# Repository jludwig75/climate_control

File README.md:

# Climate Control #

## Schematic ##

## PCB Board ##

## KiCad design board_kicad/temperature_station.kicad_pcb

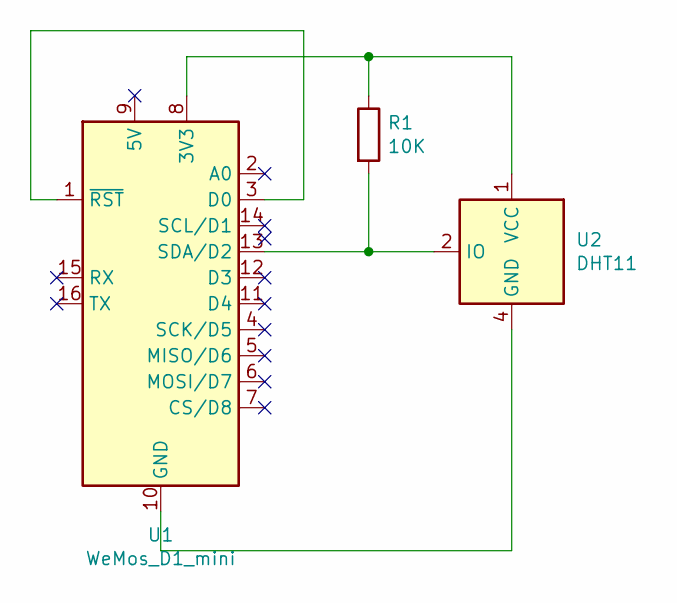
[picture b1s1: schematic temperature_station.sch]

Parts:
R1: 10K; R_Axial_DIN0207_L6.3mm_D2.5mm_P10.16mm_Horizontal
U1: WeMos_D1_mini; WEMOS_D1_mini_light
U2: DHT11; Aosong_DHT11_5.5x12.0_P2.54mm

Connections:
unnamed: R1.1, U1.8 (3V3), U2.1 (VCC)
unnamed: R1.2, U1.13 (SDA/D2), U2.2 (IO)
unnamed: U1.1 (~RST), U1.3 (D0)
unnamed: U1.10 (GND), U2.4 (GND)

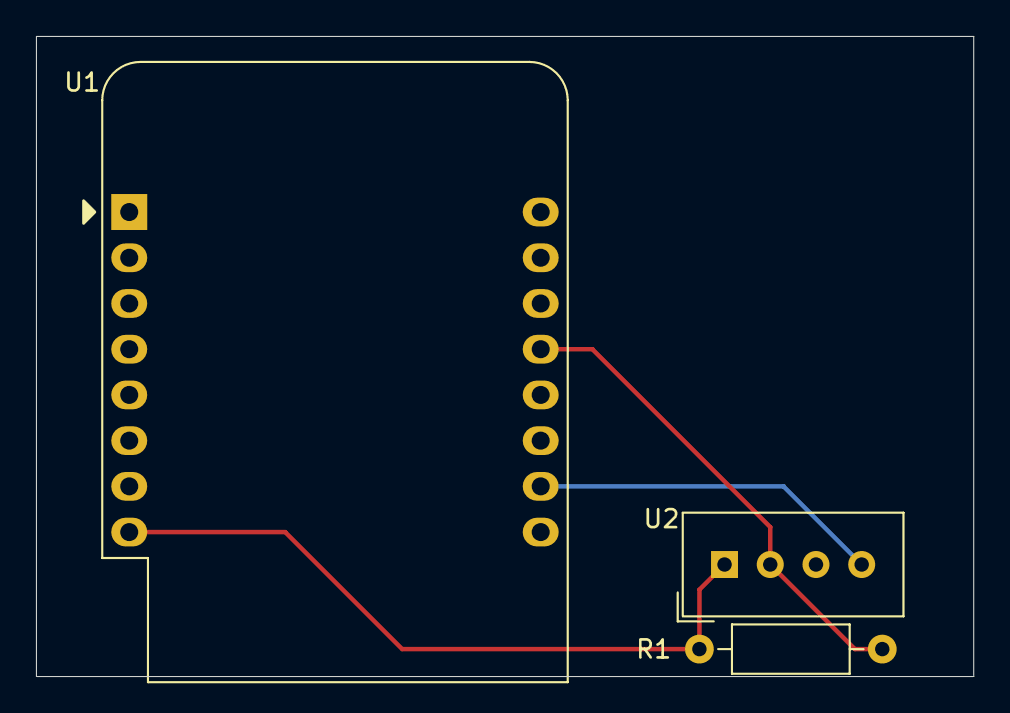
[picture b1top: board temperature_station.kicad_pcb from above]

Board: 2 copper layers, 52.1 x 35.6 mm, 3 parts (0 on the bottom side), 4 nets.

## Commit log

2020-12-19 Created repo
2020-12-19 Added control server
2020-12-19 Make control server script executable
2020-12-19 Start creating database
2020-12-19 Created database interface
2020-12-19 Added database interface test
2020-12-19 Fix ups to createDatabase and added method documentation
2020-12-19 Added 24-hour report display
2020-12-19 Report temperature as floating point
2020-12-19 Fix C++ compile errors
2020-12-20 Missed floating point conversion bug
2020-12-20 Store temperature in DB as float
2020-12-20 Set board to ESP-12E
2020-12-20 Fixed handle leak
2020-12-20 Cap vent sensor temperature to it can be viewed on the same graphs without messing up the range
2020-12-20 Bug fixes and enhancements
2020-12-20 Changed graph x axis to time uints
2020-12-20 Got refresh working
2020-12-21 Calculate and display thermostat state
2020-12-21 Impoved thermostat state calculation accuracy
2020-12-31 Added comment
2020-12-31 Added station VCC to report data
2020-12-31 Bug fixes
2020-12-31 Fix client bug
2020-12-31 Added OTA support
2020-12-31 Added webserver support for OTA initiation
2020-12-31 Split out seperate build envs in platformio.ini
2020-12-31 Moved station ID to platformio.ini
2020-12-31 Moved hostname to platformio.ini
2020-12-31 Put time limit on sensor data query
2020-12-31 Web page bug. Also only fetch as many data points as we plan to display
2020-12-31 Converted report webpage to vuej.js
2020-12-31 Fix ups
2021-01-01 Improved graph title
2021-01-01 Seprated control and report web servers. Made chart vue.js component.
2021-01-01 Added plots for all data points
2021-01-01 Fixed up variable names
2021-01-01 Removed static dir support from control server
2021-01-01 Add stations dynamically, supporting unlimited number of stations
2021-01-01 Cleanup plot code.
2021-01-01 Add plot legend
2021-01-01 Plural was wrong for plots
2021-01-01 Added ability to change end time for plot. Still needs cleanup
2021-01-02 Basic functionality to change days with forward and back buttons. Still a bug and enhancement.
2021-01-02 Changed date/time adjust interval to be display interval
2021-01-02 Display current station data on plot legend
2021-01-02 Add button to move historical data view to now.
2021-01-05 DB code fixes
2021-01-06 Start transition to MQTT
2021-01-07 Switch sensor data updates to mqtt
2021-01-07 Specify sensor data update message type
2021-01-07 Strat moving update control to MQTT
2021-01-07 Added missing files. Got MQTT update started
2021-01-07 More work on update control script
2021-01-07 Fixups to update control script
2021-01-08 Added new update script with mock station for test
2021-01-08 Broke down mock station code to match sketch modules
2021-01-08 Fixed OTA simulation bug
2021-01-08 MQTT Transition Complete: Moved update control to MQTT
2021-01-08 Removed HTTP control server
2021-01-08 Narrowed down subscription for record server
2021-01-08 Made start update message more noticable
2021-01-09 Code cleanup: remove duplication, organize code
2021-01-09 Added client type to MQTT paths
2021-01-09 Make client type configurable for ClimateMqttClient
2021-01-09 Made climate client-specific publish method. Created topics.py
2021-01-09 Move all client and message types to climate.topics.py
2021-01-09 Removed last vestiges of http from client
2021-01-09 Moved python mqtt paramaters to config file
2021-01-09 Added HVAC controller to topic conversations
2021-01-09 Started HVAC controller script
2021-01-09 Allow subscription to different client types
2021-01-09 Setup hvac controller to run as test mock
2021-01-09 Added basic control server framework
2021-01-10 Got something basic working for test
2021-01-10 Added thermostat policy with averaging policy. Issue #2
2021-01-10 Added ability to change station priorities for averaging
2021-01-10 Added note to move station priority weights to database
2021-01-12 Created service files for recorder and reporter servers
2021-01-13 Added HVAC controller policy and unit test
2021-01-14 Added unit test for hvac controller
2021-01-14 Started HVAC controller integration test
2021-01-14 Added script to run all tests
2021-01-14 Added more integration tests. Have intermitent timing bug to fix
2021-01-14 Simplified HVAC controller start up
2021-01-14 Save debug launch profile in integration test
2021-01-14 Completed hvac control integration test. Had to slow test down for MQTT server
2021-01-14 Fixed error parsing invalid sensor data
2021-01-14 Created services for climate controller and hvac controller
    Also set service to start after mosquitto
2021-01-14 Configure services to flush stdout
2021-01-15 Move record and control server modules to climate package
2021-01-15 Added control server integration test. Made test clients not interfere with production clients
2021-01-15 Improve run-tests script
2021-01-15 Fixed memory leak with timer
2021-01-16 Added scheuler client and set-mode script
2021-01-20 Move DHT22 pin definition to platformio.ini
2021-01-20 Added KiCad board project
2021-01-20 Changed DHT11 to DHT22
2021-01-21 Rearranged station ids
2021-01-21 Provide a way to release a station from update
2021-01-21 Added schedule to database. Needs a real python unit test
2021-01-22 Moved stationdb module to climate package and added station db test
2021-01-22 Moved database tests to actual unit test file
2021-01-22 Setup database tests to use test database
2021-01-22 Made basic database schedule test more meaningful
2022-10-02 Fixed bugs from library updates
